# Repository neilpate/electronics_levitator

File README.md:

Schematic:

PCB

3D Model of structure

Finished item

Video here: 
https://github.com/neilpate/electronics_levitator/blob/main/Videos/1000012148.mp4

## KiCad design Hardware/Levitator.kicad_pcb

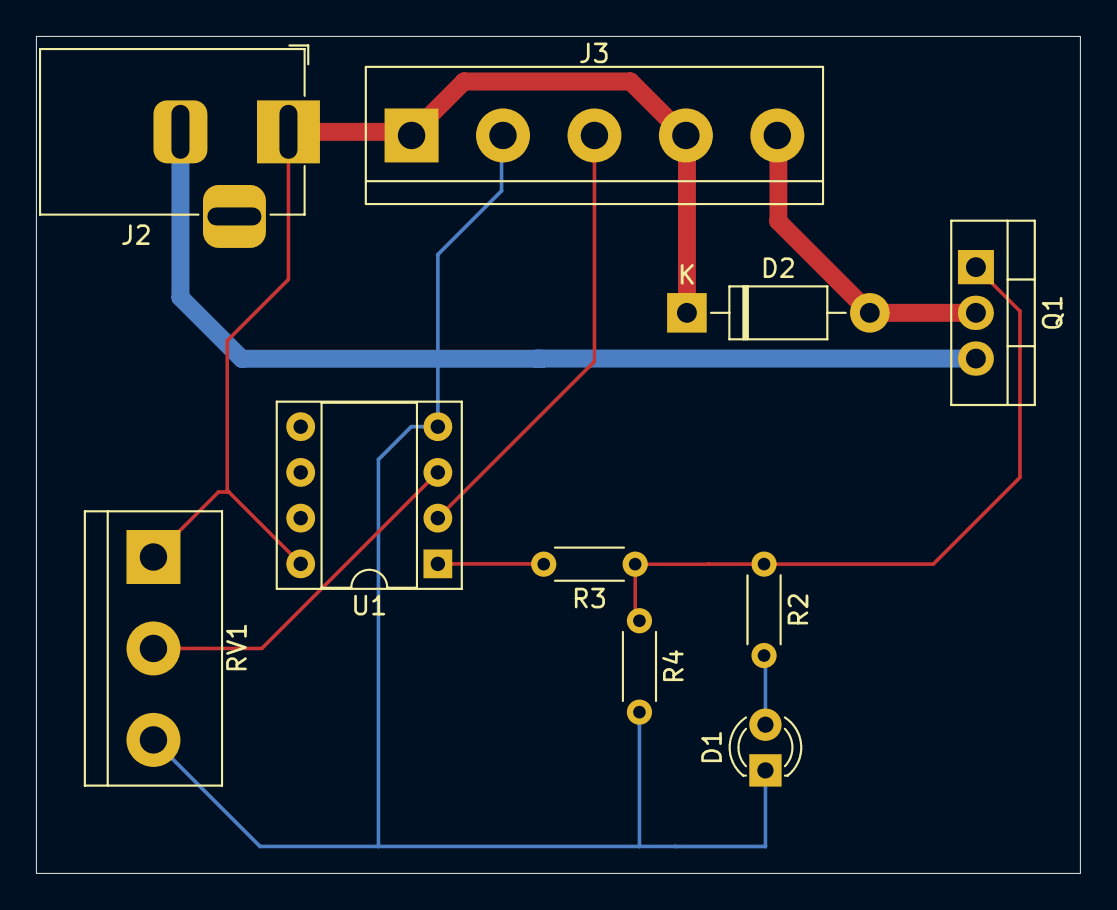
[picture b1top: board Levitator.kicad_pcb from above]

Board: 2 copper layers, 58.0 x 46.5 mm, 10 parts (0 on the bottom side), 8 nets.

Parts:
D1: LED; LED_D3.0mm
D2: 1N4007; D_DO-41_SOD81_P10.16mm_Horizontal
J2: Barrel_Jack; BarrelJack_Horizontal
J3: Screw_Terminal_01x05; TerminalBlock_bornier-5_P5.08mm
Q1: AOD4184A; TO-220-3_Vertical
R2: 1k8; R_Axial_DIN0204_L3.6mm_D1.6mm_P5.08mm_Horizontal
R3: 100; R_Axial_DIN0204_L3.6mm_D1.6mm_P5.08mm_Horizontal
R4: 10k; R_Axial_DIN0204_L3.6mm_D1.6mm_P5.08mm_Horizontal
RV1: R10k; TerminalBlock_bornier-3_P5.08mm
U1: LM358; DIP-8_W7.62mm_Socket

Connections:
/COIL-: D2.2 (A), J3.5, Q1.2 (D)
/HALL_OUT: J3.3, U1.2 (-)
GND: D1.1 (K), J2.2, J3.2, Q1.3 (S), R4.2, RV1.3, U1.4 (V-)
unnamed: D1.2 (A), R2.2
unnamed: Q1.1 (G), R2.1, R3.1, R4.1
unnamed: R3.2, U1.1
unnamed: RV1.2, U1.3 (+)
VCC: D2.1 (K), J2.1, J3.1, J3.4, RV1.1, U1.8 (V+)

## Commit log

2024-03-05 feat: Added KiCad ignore file
2024-03-05 feat: Initial schematic
2024-03-05 feat: Added video
2024-03-05 feat: Modified to use dual supplies, and tidied up
2024-03-18 feat: Updated schematic to use single MOSFET and added PCB layout
2024-03-21 feat: Moved power in to barrel socket
2024-04-11 Added photo
2024-04-11 Added another video
2024-04-11 Added videos
2024-04-11 Renamed original video
2024-04-11 Fixed video name
2025-11-23 feat: Upgraded project to KiCAD 9.0
    Also created step file
2025-11-23 feat: Added Fusion 360 models and exported STL
2025-11-23 doc: Update README with new images and video links
2025-11-23 doc: Added video
